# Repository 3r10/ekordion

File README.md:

# EKordion

## Introduction

Creation of a digital button accordion. *EK* could mean :

- The author's initials.
- *Electronic Keyboard*.

## Hardware

### PCBs *(designed with Kicad)*

+ Right hand PCB
  - 35 Cherry MX switches
  - 5 shift registers (74hc165)
  - Daisy-chain : *not implemented*
  - 6 pin connector to be connected to a micro-controller *(Arduino, ESP32, ...)*
  - Pull-down resistors : pushing buttons means high level
+ Left hand PCB :
  - 24 Cherry MX switches
  - 3 shift registers (74hc165)
  - Daisy-chain : *available*
  - 7 pin output connector to be connected to a micro-controller *(Arduino, ESP32, ...)*
  or another PCB
  - Jumper for CLK INH pull-down
  - 6 pin input connector to be connected to another PCB
  - Jumper for serial input pull-up
  - Pull-up resistors : pushing buttons means low level.

### 3D prints and laser cut *(designed with OpenSCAD)*

+ Right hand
  - 35 button caps to fit the Cherry MX switches
+ Left hand 
  - 24 button caps to fit the CHerry MX switches with offset to allow 
  the required layout.
  - laser cutted grid

## Software

### ESP32 *(IDF environment)*

Polyphonic sound synthesizer.

+ Keyboard inputs via GPIOs
+ Sound output via I2S protocol and external DAC.
+ Control of synthesis parameters via classic bluetooth
+ Synthesis engine :
  - Three instruments : bass, chords, lead
  - Wavetable synthesis
  - 10 polyphonic sounds *(may be more)*
  - Vibrato
  - Small reverberation

### Android app *(Android Studio)*

+ Control of synthesis parameters via classic bluetooth

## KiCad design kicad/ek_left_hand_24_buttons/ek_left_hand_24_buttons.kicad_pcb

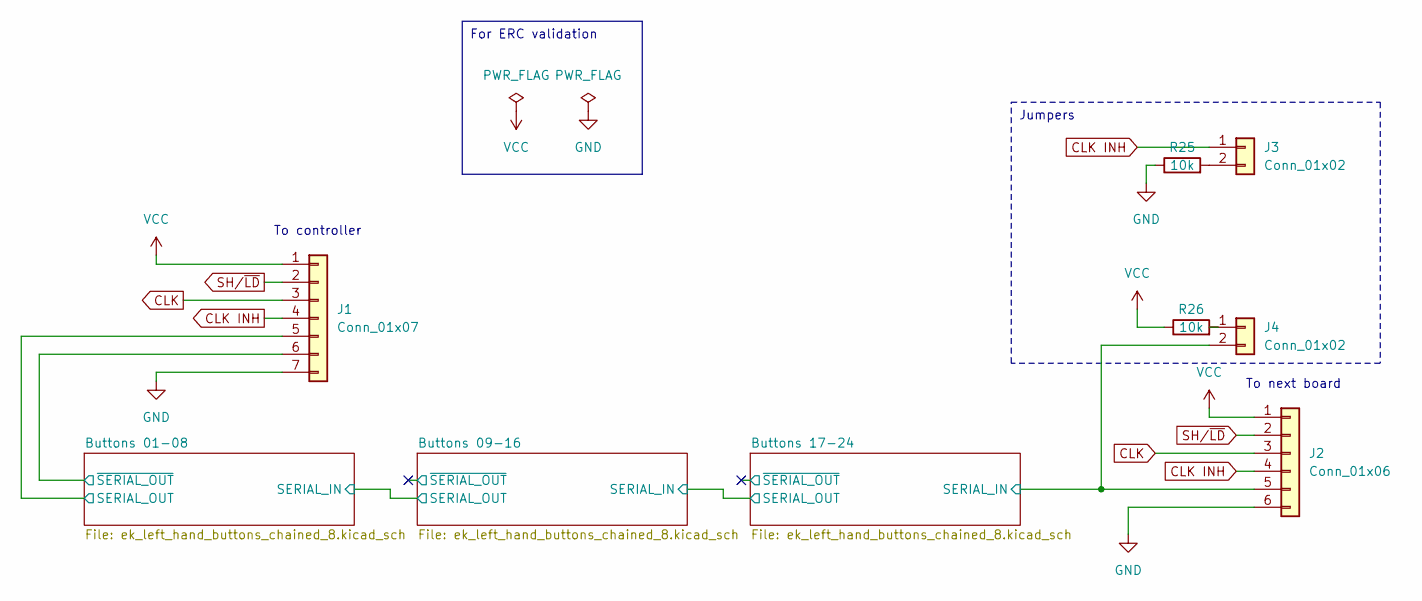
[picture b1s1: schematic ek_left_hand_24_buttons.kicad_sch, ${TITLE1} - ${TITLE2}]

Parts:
J1: Conn_01x07; PinHeader_1x07_P2.54mm_Vertical
J2: Conn_01x06; PinHeader_1x06_P2.54mm_Vertical
J3, J4: Conn_01x02; PinHeader_1x02_P2.54mm_Vertical
R25, R26: 10k; R_Axial_DIN0207_L6.3mm_D2.5mm_P10.16mm_Horizontal

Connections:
/Buttons 01-08/SERIAL_OUT: J1.5; also elsewhere on the board
/Buttons 01-08/~SERIAL_OUT: J1.6; also elsewhere on the board
/Buttons 17-24/SERIAL_IN: J2.5, J4.2; also elsewhere on the board
CLK: J1.3, J2.3; also elsewhere on the board
CLK INH: J1.4, J2.4, J3.1; also elsewhere on the board
GND: J1.7, J2.6, R25.1; also elsewhere on the board
unnamed: J3.2, R25.2
unnamed: J4.1, R26.2
SH/~LD: J1.2, J2.2; also elsewhere on the board
VCC: J1.1, J2.1, R26.1; also elsewhere on the board

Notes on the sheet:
For ERC validation
Jumpers
To controller
To next board

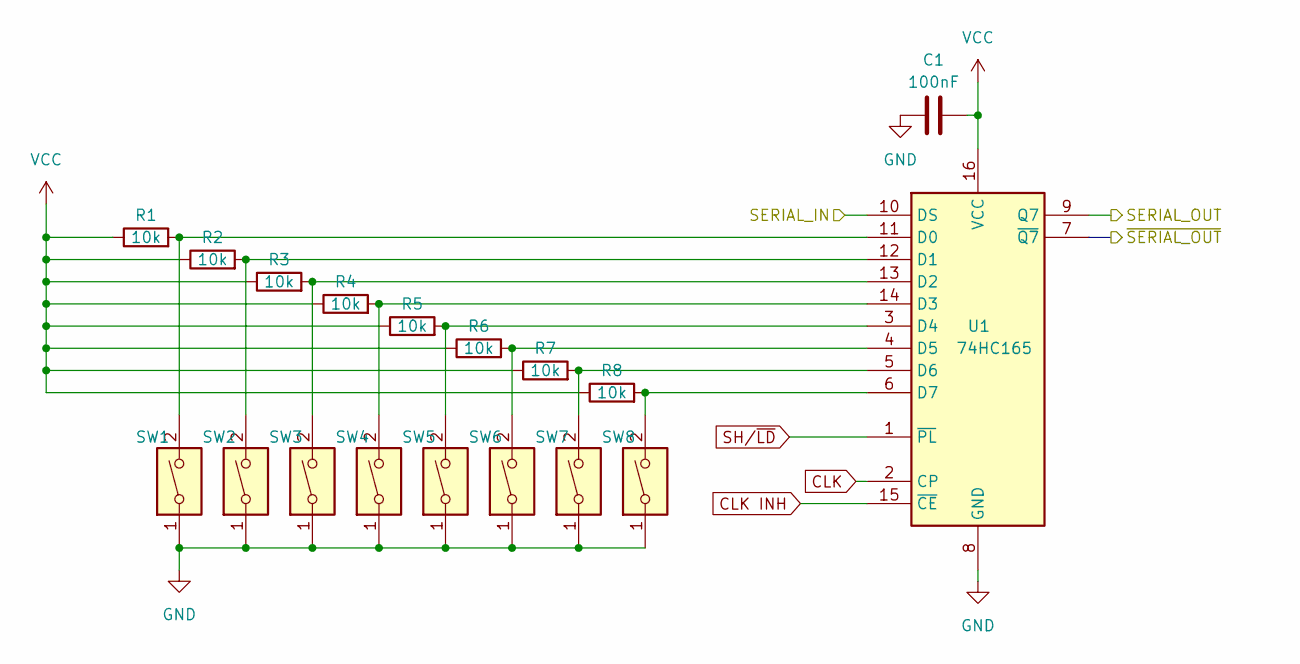
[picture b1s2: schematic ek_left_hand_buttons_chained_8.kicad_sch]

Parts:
C1: 100nF; C_Rect_L7.0mm_W2.5mm_P5.00mm
R1, R2, R3, R4, R5, R6, R7, R8: 10k; R_Axial_DIN0207_L6.3mm_D2.5mm_P10.16mm_Horizontal
SW1, SW2, SW3, SW4, SW5, SW6, SW7, SW8: SW_Cherry_MX_1.00u_PCB
U1: 74HC165; DIP-16_W7.62mm

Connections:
/Buttons 01-08/SERIAL_IN: U1.10 (DS); also elsewhere on the board
/Buttons 01-08/SERIAL_OUT: U1.9 (Q7); also elsewhere on the board
/Buttons 01-08/~SERIAL_OUT: U1.7 (~Q7); also elsewhere on the board
CLK: U1.2 (CP); also elsewhere on the board
CLK INH: U1.15 (~CE); also elsewhere on the board
GND: C1.2, SW1.1, SW2.1, SW3.1, SW4.1, SW5.1, SW6.1, SW7.1, SW8.1, U1.8 (GND); also elsewhere on the board
unnamed: R1.2, SW1.2, U1.11 (D0)
unnamed: R2.2, SW2.2, U1.12 (D1)
unnamed: R3.2, SW3.2, U1.13 (D2)
unnamed: R4.2, SW4.2, U1.14 (D3)
unnamed: R5.2, SW5.2, U1.3 (D4)
unnamed: R6.2, SW6.2, U1.4 (D5)
unnamed: R7.2, SW7.2, U1.5 (D6)
unnamed: R8.2, SW8.2, U1.6 (D7)
SH/~LD: U1.1 (~PL); also elsewhere on the board
VCC: C1.1, R1.1, R2.1, R3.1, R4.1, R5.1, R6.1, R7.1, R8.1, U1.16 (VCC); also elsewhere on the board

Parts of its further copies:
C2, C3: 100nF; C_Rect_L7.0mm_W2.5mm_P5.00mm
R9, R10, R11, R12, R13, R14, R15, R16, R17, R18, R19, R20, R21, R22, R23, R24: 10k; R_Axial_DIN0207_L6.3mm_D2.5mm_P10.16mm_Horizontal
SW9, SW10, SW11, SW12, SW13, SW14, SW15, SW16, SW17, SW18, SW19, SW20, SW21, SW22, SW23, SW24: SW_Cherry_MX_1.00u_PCB
U2, U3: 74HC165; DIP-16_W7.62mm

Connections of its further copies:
/Buttons 01-08/SERIAL_IN: U2.9 (Q7); also elsewhere on the board
/Buttons 09-16/SERIAL_IN: U2.10 (DS), U3.9 (Q7)
/Buttons 09-16/~SERIAL_OUT: U2.7 (~Q7)
/Buttons 17-24/SERIAL_IN: U3.10 (DS); also elsewhere on the board
/Buttons 17-24/~SERIAL_OUT: U3.7 (~Q7)
CLK: U2.2 (CP), U3.2 (CP); also elsewhere on the board
CLK INH: U2.15 (~CE), U3.15 (~CE); also elsewhere on the board
GND: C2.2, C3.2, SW9.1, SW10.1, SW11.1, SW12.1, SW13.1, SW14.1, SW15.1, SW16.1, SW17.1, SW18.1, SW19.1, SW20.1, SW21.1, SW22.1, SW23.1, SW24.1, U2.8 (GND), U3.8 (GND); also elsewhere on the board
unnamed: R9.2, SW9.2, U2.11 (D0)
unnamed: R10.2, SW10.2, U2.12 (D1)
unnamed: R11.2, SW11.2, U2.13 (D2)
unnamed: R12.2, SW12.2, U2.14 (D3)
unnamed: R13.2, SW13.2, U2.3 (D4)
unnamed: R14.2, SW14.2, U2.4 (D5)
unnamed: R15.2, SW15.2, U2.5 (D6)
unnamed: R16.2, SW16.2, U2.6 (D7)
unnamed: R17.2, SW17.2, U3.11 (D0)
unnamed: R18.2, SW18.2, U3.12 (D1)
unnamed: R19.2, SW19.2, U3.13 (D2)
unnamed: R20.2, SW20.2, U3.14 (D3)
unnamed: R21.2, SW21.2, U3.3 (D4)
unnamed: R22.2, SW22.2, U3.4 (D5)
unnamed: R23.2, SW23.2, U3.5 (D6)
unnamed: R24.2, SW24.2, U3.6 (D7)
SH/~LD: U2.1 (~PL), U3.1 (~PL); also elsewhere on the board
VCC: C2.1, C3.1, R9.1, R10.1, R11.1, R12.1, R13.1, R14.1, R15.1, R16.1, R17.1, R18.1, R19.1, R20.1, R21.1, R22.1, R23.1, R24.1, U2.16 (VCC), U3.16 (VCC); also elsewhere on the board

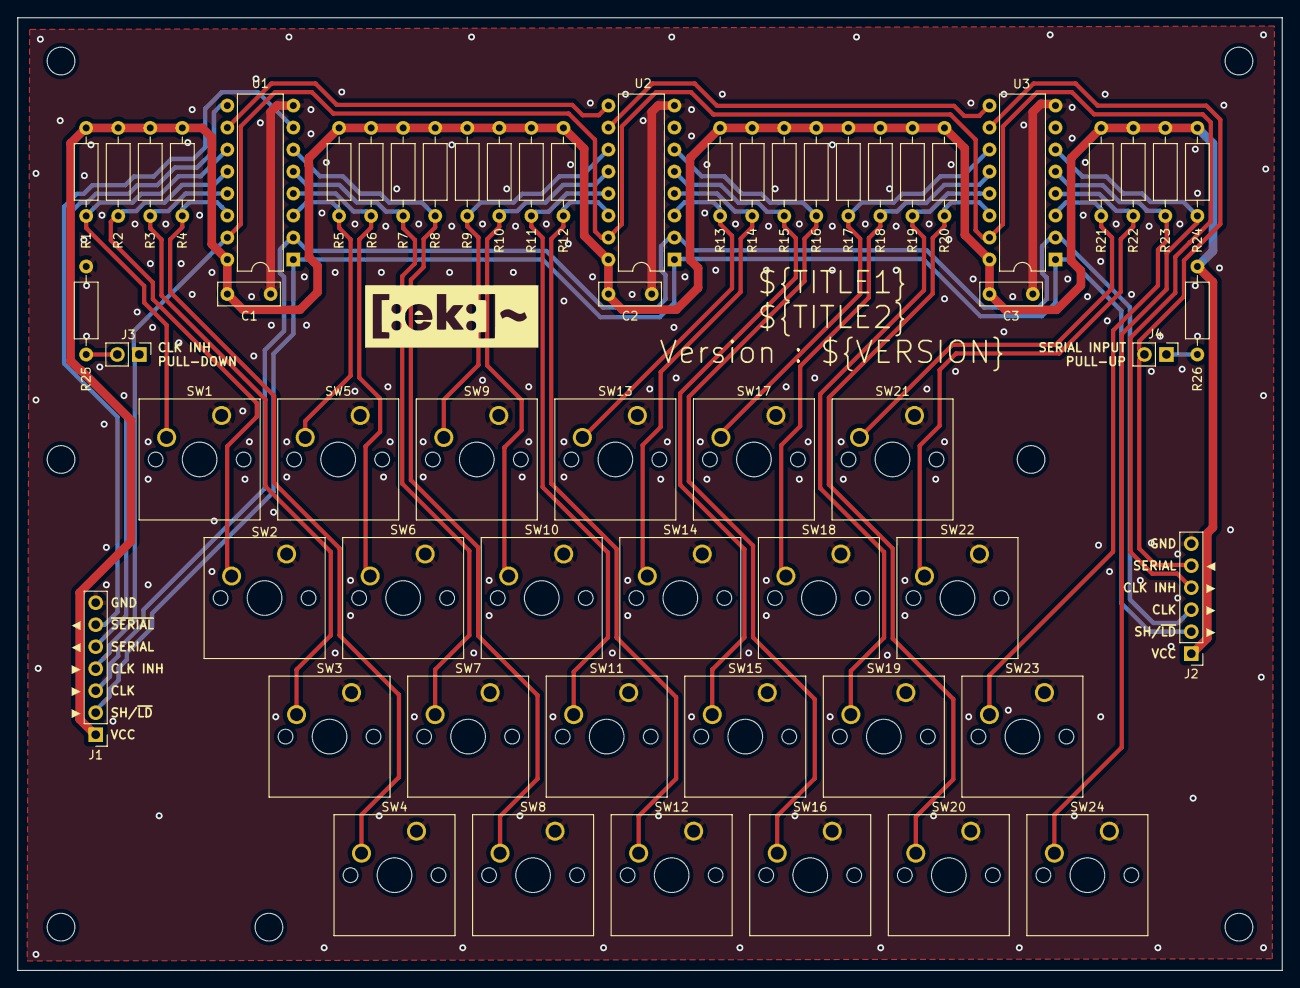
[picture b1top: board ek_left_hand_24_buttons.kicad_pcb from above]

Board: 2 copper layers, 146.0 x 110.0 mm, 67 parts (0 on the bottom side), 36 nets.

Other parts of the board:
M1, M1#2, M2, M3, M4, M4#2, M4#3: MountingHole_3.2mm_M3

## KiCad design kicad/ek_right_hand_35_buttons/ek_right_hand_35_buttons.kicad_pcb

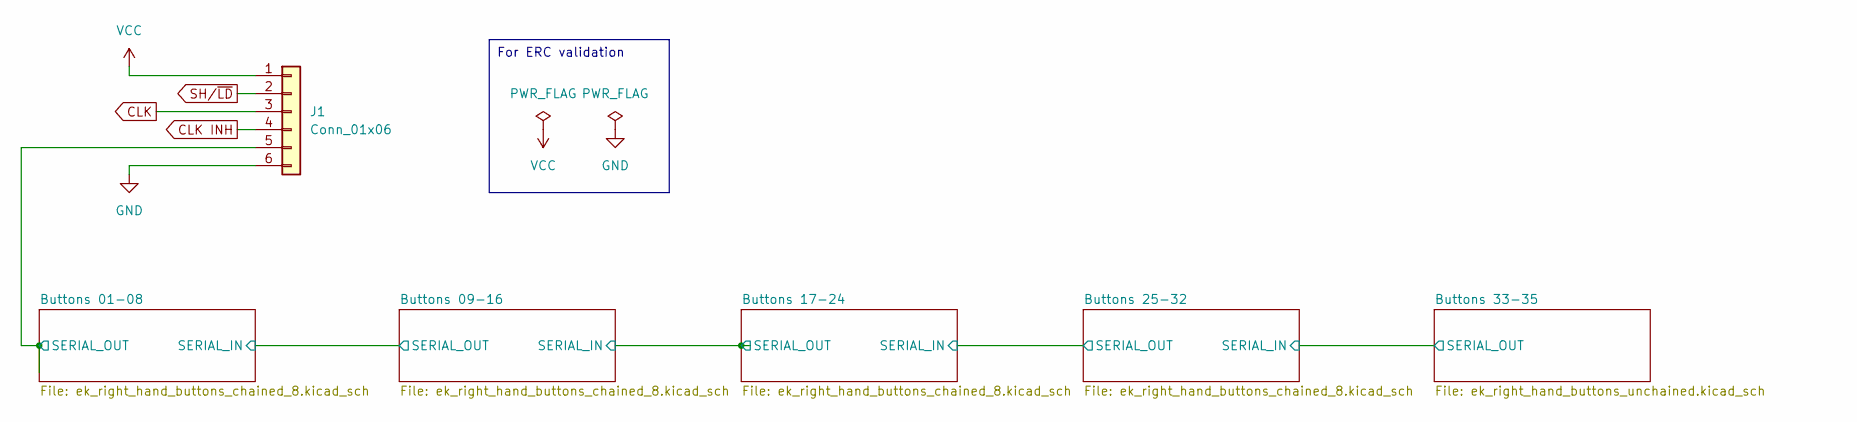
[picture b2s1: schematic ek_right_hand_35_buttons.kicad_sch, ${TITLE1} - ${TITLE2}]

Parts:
J1: Conn_01x06; PinHeader_1x06_P2.54mm_Vertical

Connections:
/Buttons 01-08/SERIAL_OUT: J1.5; also elsewhere on the board
CLK: J1.3; also elsewhere on the board
CLK INH: J1.4; also elsewhere on the board
SH/~LD: J1.2; also elsewhere on the board
VCC: J1.1; also elsewhere on the board

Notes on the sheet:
For ERC validation

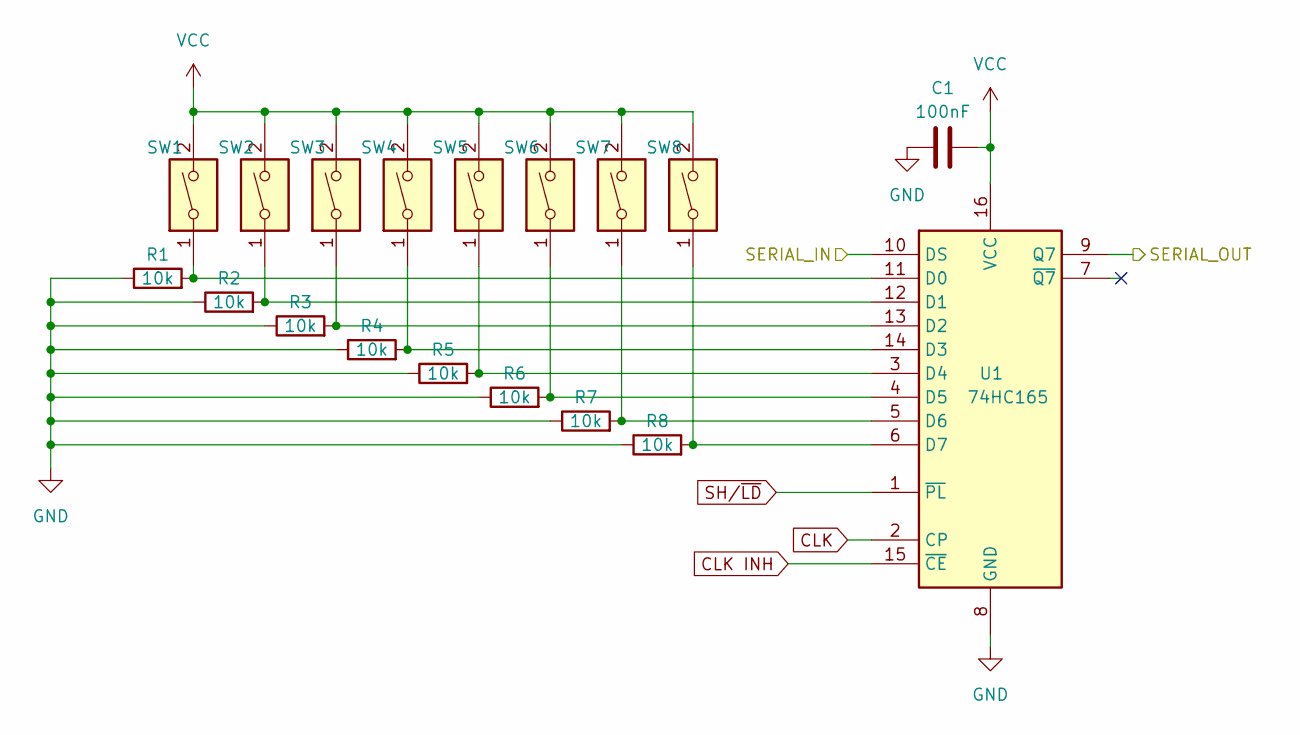
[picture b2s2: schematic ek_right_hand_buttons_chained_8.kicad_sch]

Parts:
C1: 100nF; C_Rect_L7.0mm_W2.5mm_P5.00mm
R1, R2, R3, R4, R5, R6, R7, R8: 10k; R_Axial_DIN0207_L6.3mm_D2.5mm_P10.16mm_Horizontal
SW1, SW2, SW3, SW4, SW5, SW6, SW7, SW8: SW_Cherry_MX_1.00u_PCB
U1: 74HC165; DIP-16_W7.62mm

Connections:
/Buttons 01-08/SERIAL_OUT: U1.9 (Q7); also elsewhere on the board
CLK: U1.2 (CP); also elsewhere on the board
CLK INH: U1.15 (~CE); also elsewhere on the board
unnamed: R1.2, SW1.1, U1.11 (D0)
unnamed: R2.2, SW2.1, U1.12 (D1)
unnamed: R3.2, SW3.1, U1.13 (D2)
SH/~LD: U1.1 (~PL); also elsewhere on the board
VCC: C1.1, SW1.2, SW2.2, SW3.2, SW4.2, SW5.2, SW6.2, SW7.2, SW8.2, U1.16 (VCC); also elsewhere on the board

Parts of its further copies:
C2, C3, C4: 100nF; C_Rect_L7.0mm_W2.5mm_P5.00mm
R9, R10, R11, R12, R13, R14, R15, R16, R17, R18, R19, R20, R21, R22, R23, R24, R25, R26, R27, R28, R29, R30, R31, R32: 10k; R_Axial_DIN0207_L6.3mm_D2.5mm_P10.16mm_Horizontal
SW9, SW10, SW11, SW12, SW13, SW14, SW15, SW16, SW17, SW18, SW19, SW20, SW21, SW22, SW23, SW24, SW25, SW26, SW27, SW28, SW29, SW30, SW31, SW32: SW_Cherry_MX_1.00u_PCB
U2, U3, U4: 74HC165; DIP-16_W7.62mm

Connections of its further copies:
/Buttons 09-16/SERIAL_IN: U2.10 (DS), U3.9 (Q7)
/Buttons 17-24/SERIAL_IN: U3.10 (DS), U4.9 (Q7)
/Buttons 25-32/SERIAL_IN: U4.10 (DS); also elsewhere on the board
CLK: U2.2 (CP), U3.2 (CP), U4.2 (CP); also elsewhere on the board
CLK INH: U2.15 (~CE), U3.15 (~CE), U4.15 (~CE); also elsewhere on the board
unnamed: R9.2, SW9.1, U2.11 (D0)
unnamed: R10.2, SW10.1, U2.12 (D1)
unnamed: R11.2, SW11.1, U2.13 (D2)
unnamed: R12.2, SW12.1, U2.14 (D3)
unnamed: R13.2, SW13.1, U2.3 (D4)
unnamed: R14.2, SW14.1, U2.4 (D5)
unnamed: R15.2, SW15.1, U2.5 (D6)
unnamed: R16.2, SW16.1, U2.6 (D7)
unnamed: R17.2, SW17.1, U3.11 (D0)
unnamed: R18.2, SW18.1, U3.12 (D1)
unnamed: R19.2, SW19.1, U3.13 (D2)
unnamed: R20.2, SW20.1, U3.14 (D3)
unnamed: R21.2, SW21.1, U3.3 (D4)
unnamed: R22.2, SW22.1, U3.4 (D5)
unnamed: R23.2, SW23.1, U3.5 (D6)
unnamed: R24.2, SW24.1, U3.6 (D7)
unnamed: R25.2, SW25.1, U4.11 (D0)
unnamed: R26.2, SW26.1, U4.12 (D1)
unnamed: R27.2, SW27.1, U4.13 (D2)
unnamed: R28.2, SW28.1, U4.14 (D3)
unnamed: R29.2, SW29.1, U4.3 (D4)
unnamed: R30.2, SW30.1, U4.4 (D5)
unnamed: R31.2, SW31.1, U4.5 (D6)
unnamed: R32.2, SW32.1, U4.6 (D7)
SH/~LD: U2.1 (~PL), U3.1 (~PL), U4.1 (~PL); also elsewhere on the board
VCC: C2.1, C3.1, C4.1, SW9.2, SW10.2, SW11.2, SW12.2, SW13.2, SW14.2, SW15.2, SW16.2, SW17.2, SW18.2, SW19.2, SW20.2, SW21.2, SW22.2, SW23.2, SW24.2, SW25.2, SW26.2, SW27.2, SW28.2, SW29.2, SW30.2, SW31.2, SW32.2, U2.16 (VCC), U3.16 (VCC), U4.16 (VCC); also elsewhere on the board

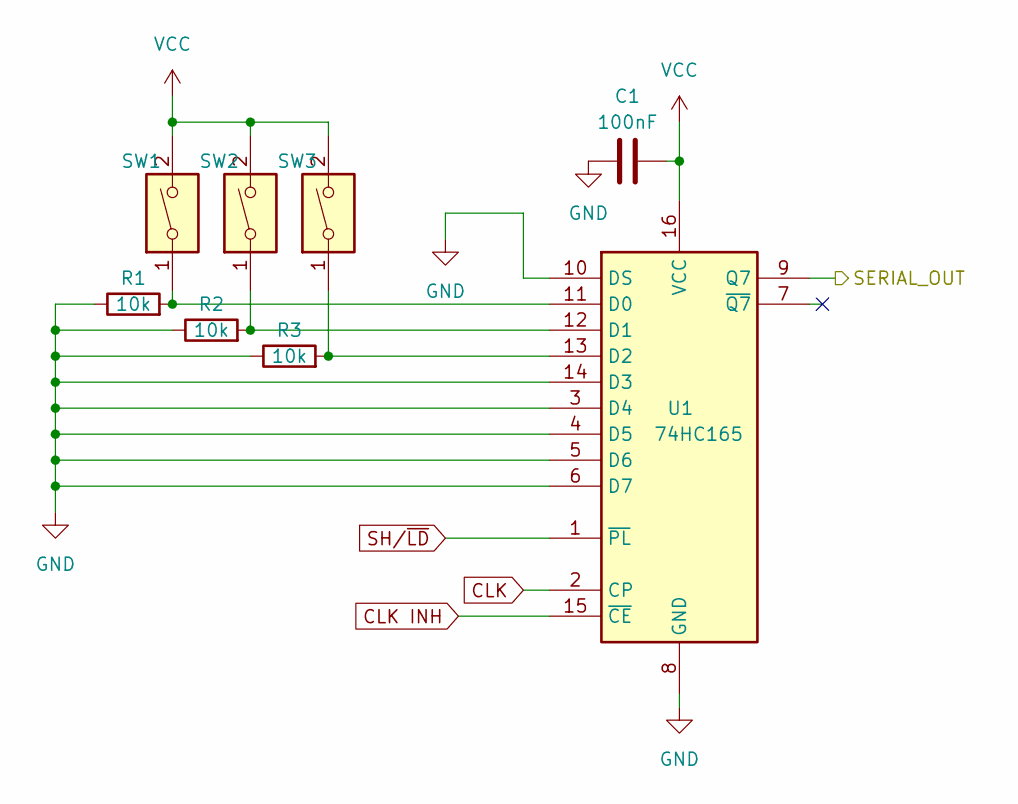
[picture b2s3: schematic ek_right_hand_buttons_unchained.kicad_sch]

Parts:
C1: 100nF; C_Rect_L7.0mm_W2.5mm_P5.00mm
R1, R2, R3: 10k; R_Axial_DIN0207_L6.3mm_D2.5mm_P10.16mm_Horizontal
SW1, SW2, SW3: SW_Cherry_MX_1.00u_PCB
U1: 74HC165; DIP-16_W7.62mm

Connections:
/Buttons 01-08/SERIAL_OUT: U1.9 (Q7); also elsewhere on the board
CLK: U1.2 (CP); also elsewhere on the board
CLK INH: U1.15 (~CE); also elsewhere on the board
unnamed: R1.2, SW1.1, U1.11 (D0)
unnamed: R2.2, SW2.1, U1.12 (D1)
unnamed: R3.2, SW3.1, U1.13 (D2)
SH/~LD: U1.1 (~PL); also elsewhere on the board
VCC: C1.1, SW1.2, SW2.2, SW3.2, U1.16 (VCC); also elsewhere on the board

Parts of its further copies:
C2, C3, C4, C5: 100nF; C_Rect_L7.0mm_W2.5mm_P5.00mm
R9, R10, R11, R17, R18, R19, R25, R26, R27, R33, R34, R35: 10k; R_Axial_DIN0207_L6.3mm_D2.5mm_P10.16mm_Horizontal
SW9, SW10, SW11, SW17, SW18, SW19, SW25, SW26, SW27, SW33, SW34, SW35: SW_Cherry_MX_1.00u_PCB
U2, U3, U4, U5: 74HC165; DIP-16_W7.62mm

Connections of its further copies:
/Buttons 09-16/SERIAL_IN: U2.10 (DS), U3.9 (Q7)
/Buttons 17-24/SERIAL_IN: U3.10 (DS), U4.9 (Q7)
/Buttons 25-32/SERIAL_IN: U4.10 (DS), U5.9 (Q7)
CLK: U2.2 (CP), U3.2 (CP), U4.2 (CP), U5.2 (CP); also elsewhere on the board
CLK INH: U2.15 (~CE), U3.15 (~CE), U4.15 (~CE), U5.15 (~CE); also elsewhere on the board
unnamed: R9.2, SW9.1, U2.11 (D0)
unnamed: R10.2, SW10.1, U2.12 (D1)
unnamed: R11.2, SW11.1, U2.13 (D2)
unnamed 12: U2.14 (D3); also elsewhere on the board
unnamed 13: U2.3 (D4); also elsewhere on the board
unnamed 14: U2.4 (D5); also elsewhere on the board
unnamed 15: U2.5 (D6); also elsewhere on the board
unnamed 16: U2.6 (D7); also elsewhere on the board
unnamed: R17.2, SW17.1, U3.11 (D0)
unnamed: R18.2, SW18.1, U3.12 (D1)
unnamed: R19.2, SW19.1, U3.13 (D2)
unnamed 20: U3.14 (D3); also elsewhere on the board
unnamed 21: U3.3 (D4); also elsewhere on the board
unnamed 22: U3.4 (D5); also elsewhere on the board
unnamed 23: U3.5 (D6); also elsewhere on the board
unnamed 24: U3.6 (D7); also elsewhere on the board
unnamed: R25.2, SW25.1, U4.11 (D0)
unnamed: R26.2, SW26.1, U4.12 (D1)
unnamed: R27.2, SW27.1, U4.13 (D2)
unnamed 28: U4.14 (D3); also elsewhere on the board
unnamed 29: U4.3 (D4); also elsewhere on the board
unnamed 30: U4.4 (D5); also elsewhere on the board
unnamed 31: U4.5 (D6); also elsewhere on the board
unnamed 32: U4.6 (D7); also elsewhere on the board
unnamed: R33.2, SW33.1, U5.11 (D0)
unnamed: R34.2, SW34.1, U5.12 (D1)
unnamed: R35.2, SW35.1, U5.13 (D2)
SH/~LD: U2.1 (~PL), U3.1 (~PL), U4.1 (~PL), U5.1 (~PL); also elsewhere on the board
VCC: C2.1, C3.1, C4.1, C5.1, SW9.2, SW10.2, SW11.2, SW17.2, SW18.2, SW19.2, SW25.2, SW26.2, SW27.2, SW33.2, SW34.2, SW35.2, U2.16 (VCC), U3.16 (VCC), U4.16 (VCC), U5.16 (VCC); also elsewhere on the board

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
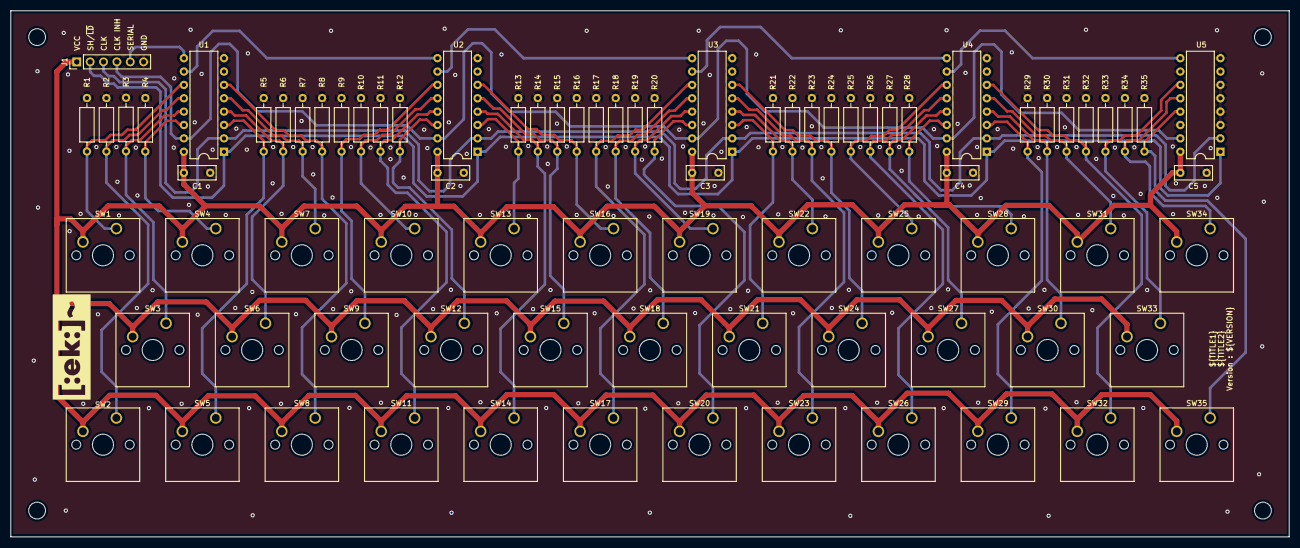
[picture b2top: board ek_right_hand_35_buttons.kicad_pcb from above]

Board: 2 copper layers, 243.0 x 100.0 mm, 85 parts (0 on the bottom side), 45 nets.

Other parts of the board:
M1, M2, M3, M4: MountingHole_3.2mm_M3

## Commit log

2023-09-05 FIrst general README
2023-09-05 EK logo
2023-09-05 Righ hand 35 first schematic
2023-09-05 Righ hand 35 first PCB with very bad tracks
2023-09-06 Right hand 35 first PCB with better tracks
2023-09-07 First right hand button test
2023-09-07 Right hand 35 first PCB with copper pour
2023-09-09 Right hand 35 first PCB with vias, holes & labels
2023-09-10 Right hand 35 condensed positions
2023-09-11 Right hand 35 better vias
2023-09-15 Right hand 35 vias and gerber
2023-09-20 Right hand button w/ stronger pin
2024-02-20 gitignore GCode + Data
2024-02-20 Reorga Openscad
2024-02-22 Laft hand tests
2024-03-05 Right hand soldering jig
2024-03-24 Left hand 24 buttons (first version)
2024-03-24 Left hand 24 buttons delete previous version
2024-03-31 Left Hand 24 before vias
2024-03-31 Left Hand 24 after vias
2024-03-31 Left Hand 24 gerber output
2024-04-15 Left hand laser cut proto
2024-04-15 Left hand soldering jig
2024-04-16 Left hand laser cut
2024-05-11 ESP32 synth first draft
2024-05-17 EKontrol (android) first draft
2024-05-17 some README update
2024-05-17 EKontrol images
2024-05-17 EKontrol Icons
2024-05-18 reorga
2024-05-18 Python __pycache__ gitignore
2024-05-18 BT messages : change codes
2024-05-18 first Python functions
2024-05-18 Python generated wavtables -> ek_tables.h
2024-05-18 Python generated wavtables -> ek_tables.h + android
2024-05-21 gitattributes -> linguist
2024-06-01 Python : quantization effect
2024-08-10 EKontrol : request for Bluetooth activation
2024-08-10 Triangle waveforms (50% -> sawtooth)
2024-08-10 Left hand mapping handled by ek_keyboards.c
2024-08-10 Octave controls
2024-08-11 LFO + Vibrato + Android slider
2024-08-11 3 separate channels -> synth is keyboard agnostic
2024-08-11 3 separate channel outputs -> controlable reverb mix
2024-08-11 Separate LFO function + tremolo
2024-08-12 Bitcrusher : resolution & downsampling
2024-08-12 EKontrol grouping by channel
2024-08-12 Arpeggiator
2024-08-14 EKordion renaming
2024-08-14 sanitizing : seperate LFO code
2024-08-14 sanitizing : seperate Voice code
2024-08-14 sanitizing : seperate Arpeggiator code
2024-08-14 sanitizing : seperate Channel code
2024-08-14 sanitizing : reverb inside synth
2024-08-14 sanitizing : channel parameters dispatched/localized in voices
2024-08-16 Shepard tones
2024-08-16 2 channel ins/outs : dry and wet
2024-08-16 Channel instead of voices handles octave/i_button
2024-08-16 Separate (proto) ADSR
2024-08-16 Separate phasor
2024-08-16 Vibrato outside voice
2024-08-16 Separate arpeggiator -> no more "voice"
2024-08-16 Linear full ADSR envelope
2024-08-17 Type naming channel_t/lfo_t -> ek_...
2024-08-17 adsr parameters -> in ek_adsr.c/h files
2024-08-18 ADSR controlled filters (+ a static version if necessary at some point)
2024-08-21 Multi-oscillator
2024-08-22 Homogeneisation of buffer handling (owner=caller + size) + Channel allocations
2024-08-22 Number of channels & config aer synth initialization parameters
2024-08-22 Separate polyphonic voice alloc + better ADSR
2024-08-22 Monophonic mode lastest note
2024-08-23 Mono-Poly modes : highest, arpeggios, chords
